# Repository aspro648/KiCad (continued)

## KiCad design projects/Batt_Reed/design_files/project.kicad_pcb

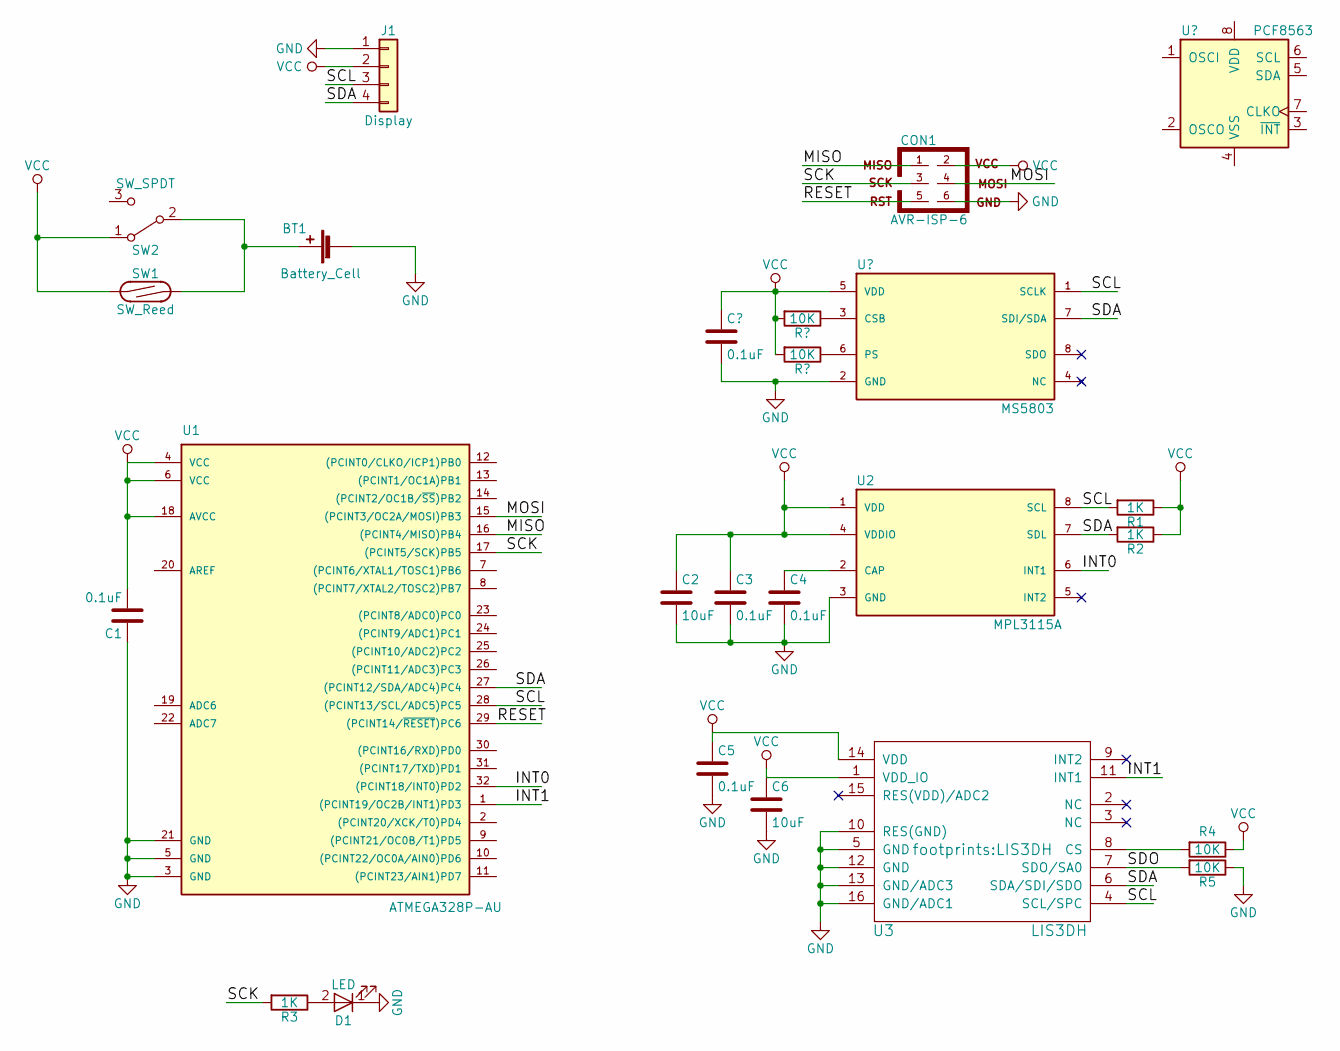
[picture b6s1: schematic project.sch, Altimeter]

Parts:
BT1: Battery_Cell; BATT_CR2032_SMD
C1, C3, C4, C5: 0.1uF; C_0805
C2, C6: 10uF; C_1206
CON1: AVR-ISP-6
D1: LED; LED_0805
J1: Display; Pin_Header_Straight_1x04_Pitch2.54mm
R1, R2, R3: 1K; R_0805
R4, R5: 10K; R_0805
SW1: SW_Reed; REED_SWITCH
SW2: SW_SPDT; SW_SPDT_CK-JS102011SAQN
U1: ATMEGA328P-AU; TQFP-32_7x7mm_Pitch0.8mm
U2: MPL3115A; LGA-8_3x5mm_Pitch1.25mm
U3: LIS3DH

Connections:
/INT0: U1.32 ((PCINT18/INT0)PD2), U2.6 (INT1)
/INT1: U1.1 ((PCINT19/OC2B/INT1)PD3), U3.11 (INT1)
/MISO: CON1.1, U1.16 ((PCINT4/MISO)PB4)
/MOSI: CON1.4, U1.15 ((PCINT3/OC2A/MOSI)PB3)
/RESET: CON1.5, U1.29 ((PCINT14/~RESET~)PC6)
/SCK: CON1.3, R3.2, U1.17 ((PCINT5/SCK)PB5)
/SCL: J1.3, R1.2, U1.28 ((PCINT13/SCL/ADC5)PC5), U2.8 (SCL), U3.4 (SCL/SPC)
/SDA: J1.4, R2.2, U1.27 ((PCINT12/SDA/ADC4)PC4), U2.7 (SDL), U3.6 (SDA/SDI/SDO)
/SDO: R5.2, U3.7 (SDO/SA0)
GND: BT1.2 (-), C1.1, C2.2, C3.2, C4.2, C5.2, C6.2, CON1.6, D1.1 (K), J1.1, R5.1, U1.3 (GND), U1.5 (GND), U1.21 (GND), U2.3 (GND), U3.5 (GND), U3.10 (RES(GND)), U3.12 (GND), U3.13 (GND/ADC3), U3.16 (GND/ADC1)
unnamed: BT1.1 (+), SW1.2, SW2.2 (B)
unnamed: C4.1, U2.2 (CAP)
unnamed: D1.2 (A), R3.1
unnamed: R4.2, U3.8 (CS)
VCC: C1.2, C2.1, C3.1, C5.1, C6.1, CON1.2, J1.2, R1.1, R2.1, R4.1, SW1.1, SW2.1 (A), U1.4 (VCC), U1.6 (VCC), U1.18 (AVCC), U2.1 (VDD), U2.4 (VDDIO), U3.1 (VDD_IO), U3.14 (VDD)

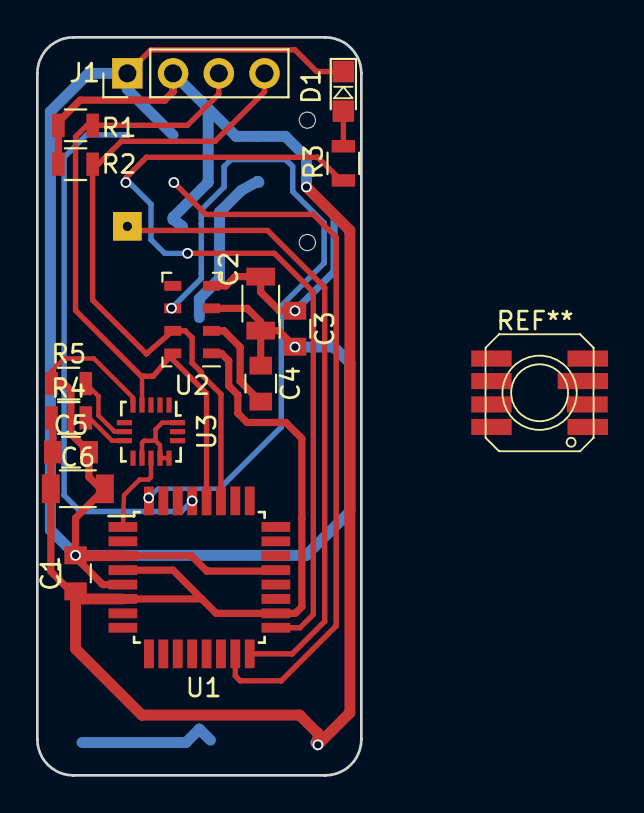
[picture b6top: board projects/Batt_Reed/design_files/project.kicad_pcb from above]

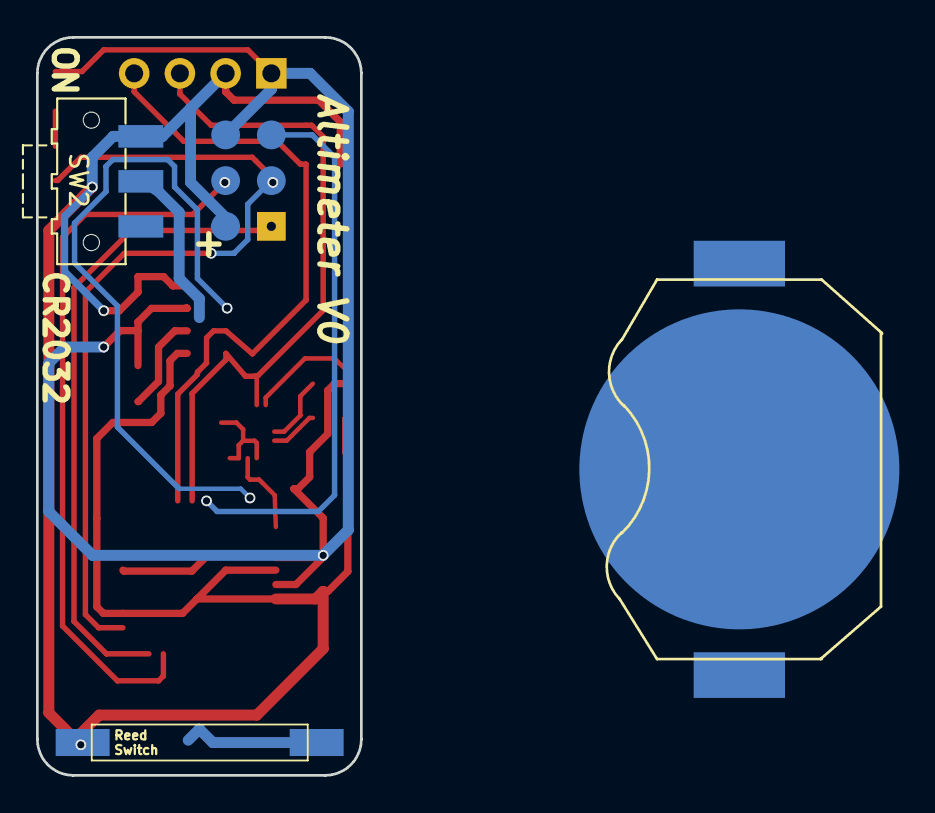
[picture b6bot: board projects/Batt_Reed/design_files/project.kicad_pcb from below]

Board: 2 copper layers, 18.0 x 41.0 mm, 20 parts (4 on the bottom side), 15 nets.

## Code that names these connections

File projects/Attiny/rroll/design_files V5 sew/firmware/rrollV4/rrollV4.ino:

/*
Heartbeat code based on Emily Lovell's LilyTiny:
http://dlnmh9ip6v2uc.cloudfront.net/datasheets/E-Textiles/Lilypad/LilyTiny.ino
https://users.soe.ucsc.edu/~emme/

Arduino pinout development based on FunShield:
https://www.tindie.com/products/MakersBox/funshield-arduino-shield-kit/

Not all Attiny cores support the tone() function. Try this one
https://github.com/SpenceKonde/ATTinyCore

ATMEL ATTINY45/85 Pin Assignments
                   +-\/-+
  Ain0 (D 5) PB5  1|    |8  Vcc
  Ain3 (D 3) PB3  2|    |7  PB2 (D 2) Ain1
  Ain2 (D 4) PB4  3|    |6  PB1 (D 1) pwm1
             GND  4|    |5  PB0 (D 0) pwm0

cd C:\Users\Maker's Box\Documents\arduino-1.6.4\hardware\tools\avr\bin
avrdude -C ..\etc\avrdude.conf -P COM12 -b 19200 -c avrisp -p attiny25 -v -e -U lfuse:w:0xE2:m -U hfuse:w:0xD7:m -U efuse:w:0xFf:m  -U flash:w:ICanSMDv25.hex


*/

int val = 500;  
int ledPin = 4;  // 
int touchPin = 3;

int on_time = 10;  // in seconds


void setup(){

  // test: with a weak pullup, the pin will read HIGH if LED in backward (no path for current)
  pinMode(touchPin, INPUT);
  digitalWrite(touchPin, HIGH);
  
  pinMode(ledPin, OUTPUT);

}



void loop(){

  digitalWrite(ledPin, HIGH);
  checkTouch();
  delay(val);
  digitalWrite(ledPin, LOW);
  delay(val);
  checkTouch();
}


bool checkTouch(){
  int touch = analogRead(touchPin);
  if (touch < 1000){
    val = val * 0.9;
    if (val < 10){
      val = 10;
    }
  }
  else{
    if(val < 500){
      val = val * 1.1;
    }
  }
}


boolean heartBeat(int on_time){
  // based on http://dlnmh9ip6v2uc.cloudfront.net/datasheets/E-Textiles/Lilypad/LilyTiny.ino

  // Variables and constants for fading pin. Needs to be a hardware PWM pin; on
  byte heartStage = 0;
  int heartBrightness = 0;
  byte heartCounter = 0;
  long off_time = millis() + on_time * 1000;

  while(millis() < off_time){
    delayMicroseconds(9999);
    // calculate brightness for heartbeat pin (by cycling 
    // through phases of pulse pattern)
    heartCounter++;
    if (heartCounter > 144) {
      heartStage = (heartStage + 1) % 4;
      heartCounter = 0;
    }
    else {
      if(checkTouch()){
        analogWrite(ledPin, heartBrightness);
      }
      else{
        digitalWrite(ledPin, LOW);
      }
      switch(heartStage) {
        case 0:         
          heartCounter += 144/12.0;
          heartBrightness += 255/12.0;
          if (heartBrightness > 255)
            heartBrightness = 255;
          break;
        case 1:
          heartCounter += 144/24.0;
          heartBrightness -= 255/24.0;
          if (heartBrightness < 0)
            heartBrightness = 0;
          break;
        case 2:
          heartCounter += 144/12.0;
          heartBrightness += 255/12.0;
          if (heartBrightness > 255)
            heartBrightness = 255;
          break;
        case 3:
          heartCounter += 144/72.0;
          heartBrightness -= 255/72.0;
          if (heartBrightness < 0)
            heartBrightness = 0;
          break;
      }//switch
    }//else
    
  }
  
  return(true);
}

/*

void blinks(int val){
  int msd = 1000;
  bool fsd = false;
  if (val == 0){
    blink(50);
  }
  else{
    while(msd > 0){
      int digit = val / msd;
      if (digit > 0){
        fsd = true; 
      }
      if (digit == 0 && fsd){
        blink(50);
      }
      for(int x=0; x < digit; x++){
        blink(500);
      }
      delay(1000); 
      val = val - msd * digit;  
      msd = msd / 10;  
    }
  }
}


void blink(int val){
  digitalWrite(ledPinPos, HIGH);
  delay(val);
  digitalWrite(ledPinPos, LOW);
  delay(val);
}

*/
